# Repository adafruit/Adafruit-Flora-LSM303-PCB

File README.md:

# Adafruit Flora LSM303 Sensor PCB
<a href="http://www.adafruit.com/products/1247"><br/>
Click here to purchase one from the Adafruit shop</a>

Add motion and direction sensing to your wearable FLORA project with this high precision 3-axis Accelerometer+Compass sensor. Inside are two sensors, one is a classic 3-axis accelerometer, which can tell you which direction is down towards the Earth (by measuring gravity) or how fast the board is accelerating in 3D space. The other is a magnetometer that can sense where the strongest magnetic force is coming from, generally used to detect magnetic north. By combining this data you can then orient yourself.

We based this sensor on the latest version of this popular sensor, the LSM303DLHC. The sensor has a digital (I2C) interface. Attaching it to the FLORA is simple: line up the sensor so its adjacent to the SDA/SCL pins and sew conductive thread from the 3V, SDA, SCL and GND pins. They line up perfectly so you will not have any crossed lines. You can only connect one of these sensors to your FLORA, but you can connect other I2C sensors/outputs by using the set of SCL/SDA pins on the opposite side.

PCB files for Adafruit Flora LSM303 sensor. The format is EagleCAD schematic and board layout
- https://www.adafruit.com/product/1247

### License

Adafruit invests time and resources providing this open source design, please support Adafruit and open-source hardware by purchasing products from [Adafruit](https://www.adafruit.com)!

All text above must be included in any redistribution

Designed by Limor Fried/Ladyada for Adafruit Industries.
Creative Commons Attribution/Share-Alike, all text above must be included in any redistribution. 
See license.txt for additional information.

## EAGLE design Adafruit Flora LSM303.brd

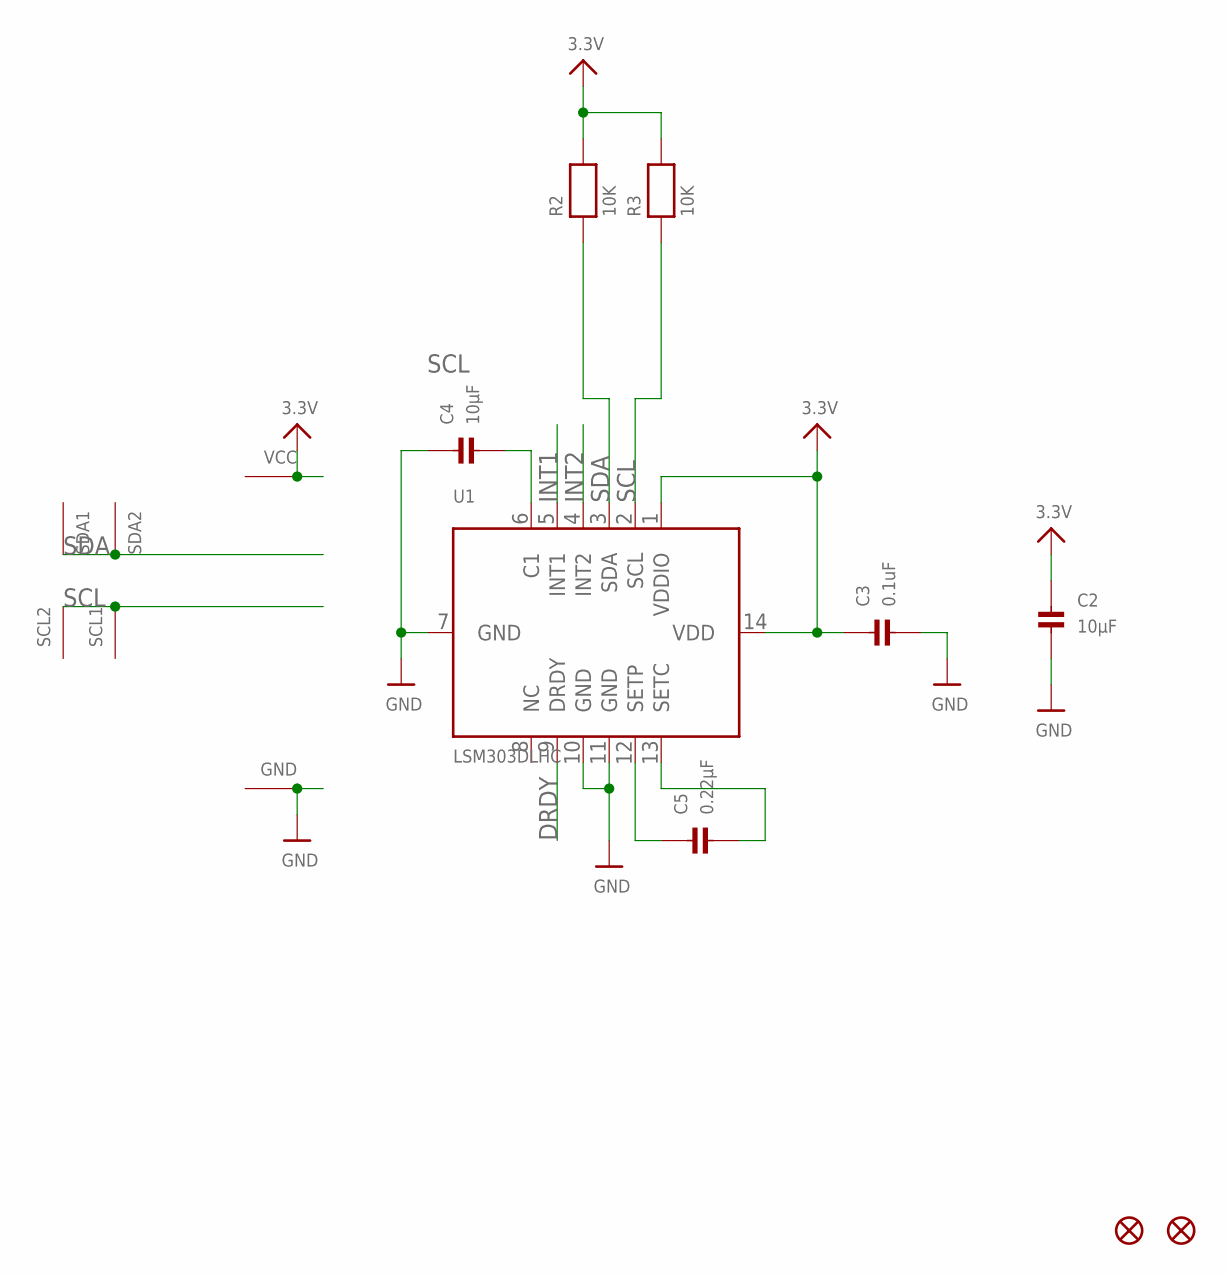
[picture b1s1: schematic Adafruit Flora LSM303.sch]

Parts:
C2, C4: 10µF; _0805
C3: 0.1uF; _0805
C5: 0.22µF; _0805
FID1, FID2: FIDUCIAL""; FIDUCIAL_1MM
GND: SEWTAP0.5IN; SEWINGTAP_0.5
R2, R3: 10K; _0805
SCL1, SCL2: SEWTAP0.5IN; SEWINGTAP_0.5
SDA1, SDA2: SEWTAP0.5IN; SEWINGTAP_0.5
U1: LSM303DLHC; LGA14
VCC: SEWTAP0.5IN; SEWINGTAP_0.5

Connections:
3.3V: C2.1, C3.1, R2.2, R3.2, U1.1 (VDDIO), U1.14 (VDD), VCC.TAP
DRDY: U1.9 (DRDY)
GND: C2.2, C3.2, C4.1, GND.TAP, U1.7 (GND), U1.10 (GND), U1.11 (GND)
INT1: U1.5 (INT1)
INT2: U1.4 (INT2)
unnamed: C4.2, U1.6 (C1)
unnamed: C5.1, U1.12 (SETP)
unnamed: C5.2, U1.13 (SETC)
SCL: R3.1, SCL1.TAP, SCL2.TAP, U1.2 (SCL)
SDA: R2.1, SDA1.TAP, SDA2.TAP, U1.3 (SDA)

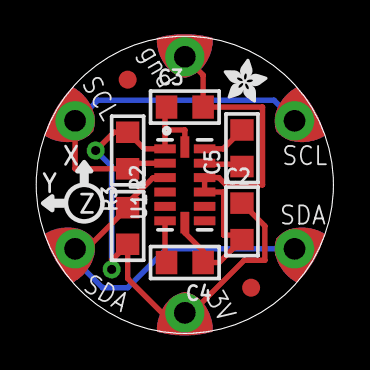
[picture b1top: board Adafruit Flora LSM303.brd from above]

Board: 2 copper layers, 16.5 x 16.5 mm, 16 parts (0 on the bottom side), 7 nets.

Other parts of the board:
U$4: ADAFRUIT_2.5MM

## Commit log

2015-03-12 init

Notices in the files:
parts and their libraries:
microbuilder: This work is placed in the public domain, and may be freely used for commercial and non-commercial work with the following conditions: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
